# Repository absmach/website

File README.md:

# Abstract Machines Website

Astro + Tailwind source for the [Abstract Machines](https://www.absmach.eu/) website and blog.

## Stack

- Astro (v5)
- Tailwind CSS

## Project Structure

- `src/pages/`: Routes (Astro pages).
- `src/components/`: Shared UI components.
- `src/layouts/`: Page layouts.
- `src/styles/`: Identity stylesheets (`identity-*.css`) shared by the layout and pages.
- `src/content/blogs/`: Blog posts (Markdown).
- `src/content.config.ts`: Blog frontmatter schema.
- `public/`: Static assets (images, favicons, etc).

## Development

```bash
npm install
npm run dev
```

Astro runs on `http://localhost:4321` by default.

During development, images and videos missing from `public/` are fetched from
`https://www.absmach.eu`, so the logo and background animations work without local
R2 credentials. An internet connection is required for these assets.

## Build & Preview

### Public website

The applied AI design is the public website at `http://localhost:4321/`.
It uses AM blue, self-hosted typography, a full-screen Paris architecture film,
and editorial photography.

- `/`: homepage, selected work, and product catalogue.
- `/products/`: searchable AI, Infrastructure, and Hardware categories.
- `/products/{slug}/`: eleven product pages, including Propeller.
- `/research/` and `/research/{elastic,confidential6g}/`: research programmes.
- `/company/`: company background and engineering approach.
- `/stories/{nokia,intel,ericsson,target}/`: sourced engineering stories.
- `/contact/`: enquiry form with product and topic preselection.

The contact form submits to the existing `/api/contact` endpoint. SMTP settings
and delivery requirements are described below. Local browser checks should
intercept submissions rather than sending real mail.

The former `/preview/ai/` page routes redirect permanently to the public pages.
Existing product URLs continue to resolve; `/synth`, `/projects`, and the two
project detail URLs redirect to their new counterparts. Redirects cover both trailing-slash forms and are excluded
from the sitemap. Public pages have canonical URLs, social metadata, and no
preview-only indexing restriction. Blog posts, guides, solutions, pricing,
legal pages, RSS, and documentation remain available at their existing URLs.

`IdentityLayout.astro` owns the main navigation, footer, and public metadata.
The product catalogue lives in `src/data/identity-products.ts`; product pages
and portfolio cards share `ProductVisual.astro`. The homepage and portfolio
show four AI products, four Infrastructure products, and three Hardware products.

Product tabs, category search, mobile navigation, video controls, and media
credits work across the public pages. The silent video pauses offscreen and
when the tab is hidden. Reduced-motion and Save-Data preferences keep the still
poster until the visitor chooses to play.

Existing media URLs remain at `public/preview/ai/media/` to preserve asset
caching. The optimized Paris film is approximately 2.9 MB; editorial photos are
WebP. `src/data/identity-photos.ts` supplies image attributes from the manifest
used by the footer credits. Attribution and source/license records are in
`video-source.json` and `photos-sources.json`. Product imagery and artwork are
recorded in `media/products/sources.json`; project, story, and membership
provenance is stored in their respective media folders. Font licenses and
source records remain in `public/preview/ai/fonts/`.

### Production build

```bash
npm run build
npm run check:site
npm run preview
```

## Cloudflare Scripts

Use the package scripts for Pages Functions workflows:

```bash
npm run cf:dev
npm run cf:deploy
```

- `cf:dev`: Builds the site and starts local Pages dev server from `dist/` using `wrangler.jsonc`.
- `cf:deploy`: Builds and deploys `dist/` to the `absmach` Cloudflare Pages project using `wrangler.jsonc`.

Note: `wrangler pages deploy` does not accept compatibility flags as CLI arguments. Keep them in `wrangler.jsonc` and in Cloudflare Pages project settings.

`wrangler.jsonc` (project config):

- `name`: Cloudflare Pages project name (the `*.pages.dev` subdomain).
- `pages_build_output_dir`: deploy output directory (`./dist`).
- `compatibility_date` and `compatibility_flags` (for example `nodejs_compat`) for Functions runtime.
- `vars`: non-secret defaults for Functions (for contact form, use `TEAM_CONTACT_EMAIL` and `MAIL_FROM_EMAIL`).

Wrangler automatically reads `wrangler.jsonc` when commands are run from the project root.

## Contact Form API (Cloudflare Pages Function)

The contact page submits to `POST /api/contact` via `src/pages/api/contact.js`.
The endpoint uses `nodemailer` over SMTP (Google SMTP supported).
Each successful submission sends:

- one email to your team inbox (`TEAM_CONTACT_EMAIL`)
- one confirmation copy to the user who submitted the form email

Request payload fields:

- `name`
- `email`
- `message`

Required environment variables:

- `SMTP_HOST`: SMTP server host (for Google: `smtp.gmail.com`).
- `SMTP_PORT`: SMTP server port (`465` for SSL, `587` for STARTTLS).
- `SMTP_SECURE`: `true` when using SSL port (usually `465`), otherwise `false`.
- `SMTP_USER`: SMTP username (for Google: full Gmail/Workspace email).
- `SMTP_PASS`: SMTP password (for Google: app password).
- `MAIL_FROM_EMAIL`: From address used when sending both emails.
- `TEAM_CONTACT_EMAIL`: Team inbox that receives contact requests.

For local `smtp4dev` testing (Docker `-p 2525:25`), use:

```bash
SMTP_HOST=127.0.0.1
SMTP_PORT=2525
SMTP_SECURE=false
SMTP_USER=
SMTP_PASS=
MAIL_FROM_EMAIL=info@absmach.eu
TEAM_CONTACT_EMAIL=info@absmach.eu
```

`SMTP_USER` and `SMTP_PASS` are optional for local test servers.

For Cloudflare Pages production:

- Non-secret values are already in `wrangler.jsonc` under `vars`:
  `SMTP_HOST`, `SMTP_PORT`, `SMTP_SECURE`, `MAIL_FROM_EMAIL`, `TEAM_CONTACT_EMAIL`.
- Set only SMTP credentials as secrets on the project:

```bash
wrangler pages secret put SMTP_USER
wrangler pages secret put SMTP_PASS
```

Backward compatibility: `NO_REPLY_EMAIL`, `CONTACT_FROM_EMAIL`, and `CONTACT_TO_EMAIL` are still accepted, but new projects should use `MAIL_FROM_EMAIL` and `TEAM_CONTACT_EMAIL`.

Production does not use `.dev.vars`.

- `.dev.vars` is local-only for `wrangler pages dev`.
- For production, configure values in Cloudflare Pages:
  Dashboard -> Pages -> your project -> Settings -> Variables and Secrets -> Production.
- No separate production env file is required in the repo.

For local Cloudflare Pages function testing, copy `.dev.vars.example` to `.dev.vars` and fill the values.

`nodemailer` requires Node compatibility in Cloudflare Workers. Enable `nodejs_compat`:

- In Cloudflare Pages project settings: Workers runtime compatibility flags.
- Or in local dev: `wrangler pages dev dist --compatibility-flag=nodejs_compat`.

## Images

Images are served from Cloudflare R2 (not committed to this repo) via
`src/pages/img/[...path].ts`, which keeps existing `/img/...` URLs working unchanged.
Maintainers publishing new/updated images: see [scripts/README.md](scripts/README.md).

## Blog

See [WRITING.md](WRITING.md) for frontmatter and writing guidelines.

## Sitemap / robots.txt

- `@astrojs/sitemap` generates `dist/sitemap-index.xml` (and chunk files like `dist/sitemap-0.xml`) during `npm run build`.
- `src/pages/robots.txt.ts` is prerendered as `/robots.txt` and points to `/sitemap-index.xml`.

## RSS

- `src/pages/rss.xml.ts` is prerendered as `/rss.xml` (blog feed).

## Documentation

- [How to Write a Blog Post](WRITING.md)
- [Publishing Images (maintainers)](scripts/README.md)

## Legal document scope

The company website’s `/terms/` covers website use, not all product contracts.
Atomic terms and privacy information remain on `atomicapp.dev/legal/`.
`/privacy/` describes company-site visits and enquiries. `/imprint/` identifies
the publisher and host. General and legal enquiries use `info@absmach.eu`; privacy
requests use `privacy@absmach.eu`. No voluntary uptime, support, return or warranty
period is offered by these website documents. Existing accepted customer agreements
are not amended by these edits.

Supplier transfer arrangements, actual mailbox/log retention and edge-injected
tracking must be checked against production configuration. A public company business
telephone remains to be supplied; the publisher’s private number is not published.
These content corrections do not certify operational compliance.

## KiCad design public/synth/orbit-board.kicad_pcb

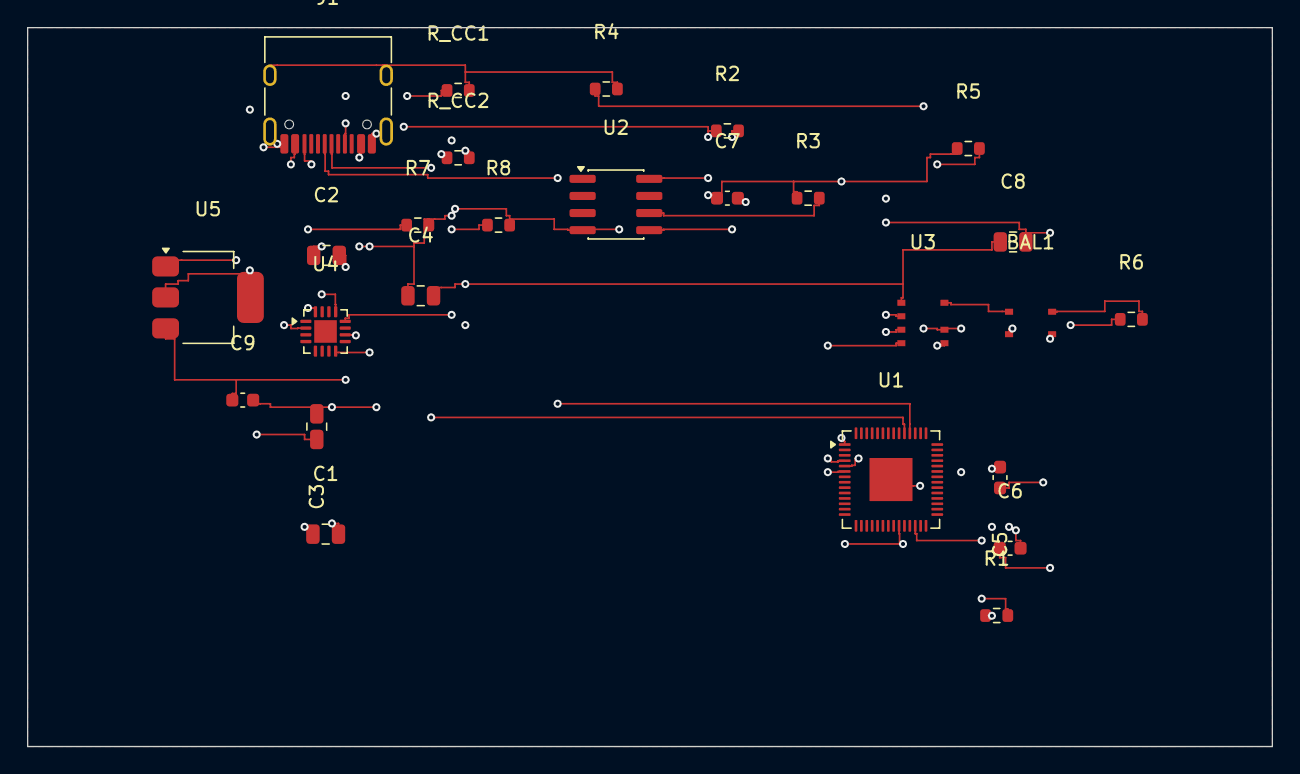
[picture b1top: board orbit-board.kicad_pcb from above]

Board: 4 copper layers, 92.5 x 53.4 mm, 26 parts (0 on the bottom side), 21 nets.

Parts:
BAL1: balun_2g4; Johanson_0805
C1, C2, C3, C4, C8: c_generic_0805; C_0805_2012Metric
C5, C6, C7, C9: c_generic_0603; C_0603_1608Metric
J1: usb_c_receptacle; USB_C_Receptacle_HRO_TYPE-C-31-M-12
R1, R2, R3, R4, R5, R6, R7, R8: r_generic_0603; R_0603_1608Metric
R_CC1, R_CC2: r_generic_0603; R_0603_1608Metric
U1: rp2350; QFN-56-1EP_7x7mm_P0.4mm_EP3.2x3.2mm
U2: atecc608; SOIC-8_3.9x4.9mm_P1.27mm
U3: bg95; Quectel_BG95-M3
U4: bq24074; VQFN-16-1EP_3x3mm_P0.5mm_EP1.68x1.68mm
U5: ams1117_3v3; SOT-223-3_TabPin2

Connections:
net_0: C1.1, J1.A4, J1.A9, J1.B4, J1.B9, U4.13
net_1: BAL1.4, C1.2, C2.2, C3.2, C4.2, C5.2, C6.2, C7.2, C8.2, C9.2, J1.A1, J1.A12, J1.B1, J1.B12, J1.SH, R4.2, R7.2, R8.2, R_CC1.2, R_CC2.2, U1.57, U2.4, U3.3, U4.8, U4.17, U5.1
net_2: J1.A5, R_CC1.1
net_3: J1.B5, R_CC2.1
net_4: C2.1, C9.1, U4.10, U5.3
net_5: C3.1, C5.1, C6.1, C7.1, R1.1, R2.1, R3.1, R5.1, U1.1, U1.23, U1.43, U1.44, U1.48, U2.8, U5.2
net_6: C4.1, C8.1, U3.32, U4.2
net_7: R7.1, U4.16
net_8: R8.1, U4.12
net_9: R1.2, U1.26
net_10: R2.2, U1.2, U2.5
net_11: R3.2, U1.3, U2.6
net_12: R4.1, U1.6, U3.15
net_13: U1.4, U3.34
net_14: U1.5, U3.35
net_15: BAL1.1, U3.60
net_16: BAL1.2, R6.1
net_17: BAL1.3, R6.2
net_18: R5.2, U3.17
net_19: J1.A6, U1.47
net_20: J1.A7, U1.46

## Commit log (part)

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2026-03-11 docs(blog): rename Proplet to Propeller in TEE article
2026-03-11 docs(blog): update title, description, and Propeller details
2026-03-11 Rename images and update references
2026-03-11 docs(blog): fix architecture image to move KSB out of tee
2026-03-12 add a changelog blog
2026-03-12 update date
2026-03-12 add requested changes
2026-03-16 initial implementation
2026-03-18 first blog draft
2026-03-18 update package json package manager
2026-03-19 add blog images
2026-03-19 fix date
2026-03-19 remove empty space
2026-03-23 add access control blog
2026-03-24 Add SuperMQ and Magistrala merge announcement blog post
2026-03-24 Add SuperMQ and Magistrala unified platform detailed blog post
2026-03-24 remove section
2026-03-24 Add cover image and fix image path for merge announcement blog
2026-03-25 Add cover image and fix image path for unified blog post
2026-03-27 Remove featured flag and add Abstract Machines stack description
2026-03-30 Remove SuperMQ references and update to Magistrala only
    - Replace all SuperMQ mentions with Magistrala throughout the blog
    - Update excerpt and descriptions to reflect unified platform
    - Remove 'built on SuperMQ' phrasing since platforms are now merged
    - Fix duplicate text and formatting issues in Domains section
2026-03-30 Update architecture diagram for access control blog
2026-04-01 address comments
2026-04-02 update date to 2nd April
2026-04-02 add agent blog
2026-04-02 remove docs links
2026-04-06 Add SuperMQ and Magistrala merge announcement blog post (#112)
    * Add SuperMQ and Magistrala merge announcement blog post
    * Add cover image and fix image path for merge announcement blog
    * Remove featured flag and add Abstract Machines stack description
    * address comments
    ---------
2026-04-07 SEO improvements: add llms.txt, meta descriptions, and schema updates for absmach.eu
2026-04-07 Fix SEO issues: canonical URLs, OG images, JSON-LD schemas, and title tags
2026-04-07 SEO report fixes
2026-04-07 Update merge blog
2026-04-07 NOISSUE - Update merger blog
2026-04-07 update cover page
2026-04-07 add new image
2026-04-09 add smart water metering blog
2026-04-09 make blog more professional
2026-04-10 add magistrala as a framework blog
2026-04-10 vault migration
2026-04-10 update wording
2026-04-13 update the date to 13th
2026-04-14 remove package lock and stick to pnpm as package manager
2026-04-20 add announcement blog
2026-04-21 empty commit to triggering CF build
2026-04-21 update number of deployments
2026-04-21 add solution packs blog
2026-04-22 fix: update intro line
2026-04-27 fix wording
2026-04-27 add best iot platforms in 2026 blog
2026-04-27 NOISSUE - Update fml blog to reflect implementation
2026-04-27 NOISSUE - Replace cover image and clean up asset names
    - Replace Federated__Machine_Learning.jpg cover with propeller-fml-mental-model.svg
    - Strip federated-ml prefix from all blog image filenames
    - Update fml.md image references to match renamed files
    - Add centralized-training-data.xml draw.io source diagram
2026-04-27 Add fml blog
    Update blog post
    Add images
    Add images
    Address comments
    Address comments
    Address comments
2026-04-27 NOISSUE - Clean up blog image names
    Remove fml/federated prefixes from remaining image filenames,
    delete unused jpg cover, and update references in fml.md.
2026-04-27 fix: update content accuracy and add external links
2026-04-27 fix: update date
2026-04-27 NOISSUE - Remove centralized-training-data.xml
2026-04-28 NOISSUE - Add fML blog (#81)
    * Add fml blog
    Update blog post
    Add images
    Add images
    Address comments
    Address comments
2026-04-28 supermq to magistrala naming changeover
2026-04-30 updated blog with migrations
2026-04-30 add migration blog
2026-04-30 update the image
2026-04-30 NOISSUE - Add migration blog for v0.20.0 (#139)
2026-04-30 change the link to blog
2026-04-30 Add v0.20.0 release blog (#134)
    * add announcement blog
    * update wording
    * address comments
    * updated blog with migrations
    * fix wording
    * update the image
2026-04-30 remove featured option
2026-04-30 add matrix link
2026-04-30 NOISSUE - Update blog (#140)
    * remove featured option
    * add matrix link
    ---------
2026-05-05 update rules engine description
2026-05-05 update when not to section for magistrala
2026-05-05 MG-137 - Add best IoT platforms in 2026 blog (#138)
    * add best iot platforms in 2026 blog
    * fix: update content accuracy and add external links
    * fix: update date
    * update rules engine description
    * update when not to section for magistrala
    ---------
2026-05-05 update blog for best iot platform in 2026
2026-05-06 MG-137 - Add best IoT platforms in 2026 blog (#138)
2026-05-06 update screenshots
2026-05-06 add tags
2026-05-06 update alts for the image
2026-05-06 add links
2026-05-07 Add FluxMQ dashboard blog (#114)
    * add flux dashbord blog
    * update screenshots
    * add tags
    * update alts for the image
    * add links
    * update date
2026-05-07 update solutions, services, projects,company and contact pages
2026-05-07 fix SEO and add docs to navbar
2026-05-07 update navbar dropdowns
2026-05-07 remove extra services from navbar
2026-05-07 update fluxmq logo and colors
2026-05-07 fix hero sections for product pages
2026-05-07 remove blue accent
2026-05-07 add global deployments
2026-05-07 utilize magistrala blue theme
2026-05-07 update the blue theme to be more distinct
2026-05-10 fix mobile responsiveness
2026-05-11 update SEO and performance
2026-05-11 fix icon visibility
2026-05-12 migration from s0 to a0
2026-05-19 add atom and quarc
2026-05-19 update deployments cards
2026-05-19 update product cards
2026-05-19 update hero image
2026-05-19 add lucide icons
2026-05-20 fix icons
2026-05-20 allow for quick theme switching
2026-05-20 Unification deployment (#144)
    * update homepage, products, blog pages
    * update solutions, services, projects,company and contact pages
    * remove extra services from navbar
    * update navbar dropdowns
    * fix SEO and add docs to navbar
    * fix hero sections for product pages
2026-05-22 add hardware page
2026-05-22 NOISSUE - Add hardware page (#146)
2026-05-22 fix quarc header description
2026-05-22 fix quarc header description (#147)
2026-05-22 fix website open-graph image
2026-05-22 fix website open-graph image (#148)
2026-05-25 fix urls
2026-05-25 fix urls (#149)
2026-05-25 fix links in blogs
2026-05-25 fix links in blogs (#150)
2026-05-25 fix abstract machines links
2026-05-25 fix abstract machines links (#151)
2026-05-26 fix mobile responsiveness for product pages
2026-05-26 fix mobile hero logo/name sizing across product pages
2026-05-26 update propeller hero section image from being clipped
2026-05-26 still show hero image in mobile mode
2026-05-26 fix organization level SEO
2026-05-26 fix product pages SEO
2026-05-26 fix heading hierarchy, keyword H2s, and internal linking
2026-05-26 fix finalcta enterprise card
2026-05-26 fix image and video CLS — add width/height attributes across all hero videos and Magistrala feature images
2026-05-26 fix mobile touch targets for blog pillar chips
2026-05-29 fix Magistrala product page SEO
2026-05-29 fix FluxMQ product page SEO
2026-05-29 fix atom product page SEO
2026-05-29 update A0 product SEO
2026-05-29 update propeller image
2026-05-29 separate propeller hero section image
2026-05-29 update propeller product page SEO
2026-05-29 remove unused architecture image
2026-05-29 add internal cross-links across product pages for pillar-cluster SEO
2026-06-02 make documentation pri cta for fluxmq
2026-06-02 add github links and make docs cta for flux
2026-06-02 update atom and propeller ctas
2026-06-04 fix solutions link to cloud
2026-06-05 NOISSUE - Update SEO (#152)
    * fix organization level SEO
    * fix product pages SEO
    * fix heading hierarchy, keyword H2s, and internal linking
    * fix finalcta enterprise card
    * fix image and video CLS — add width/height attributes across all hero videos and Magistrala feature images
    * fix mobile touch targets for blog pillar chips
2026-06-08 update sitemap file
2026-06-08 update sitemap file (#155)
2026-06-08 fix lint and formating issues
2026-06-08 update package manager version
2026-06-08 add workspace manager
2026-06-08 add node to allowed builds
2026-06-08 fix format errors
2026-06-08 fix format check
2026-06-09 NOISSUE - Remove CD, add CI, fix lint and format issues (#156)
    * fix lint and formating issues
    * update package manager version
    * add workspace manager
    * add node to allowed builds
    * fix format errors
    * fix format check
2026-06-10 add pillar pages
2026-06-12 add atom announcement blog
2026-06-12 add atom category
2026-06-12 fix formatting
2026-06-12 add ui screenshots
2026-06-12 Improve text
2026-06-12 remove scrollbar in playground image
2026-06-12 fix consecutive images to a grid format
2026-06-12 replace playground image with create role image
2026-06-12 NOISSUE - Add Atom announcement blog (#158)
    * add atom announcement blog
    * add atom category
    * fix formatting
    * add ui screenshots
    * Improve text
    * remove scrollbar in playground image
2026-06-15 add getting started with atom blog
2026-06-15 fix curl commands
2026-06-15 add mermaid functionality
2026-06-15 add atom docs to header link
2026-06-15 add getting started link in atom announcement
2026-06-15 add atom docs to header link (#160)
2026-06-15 add blog on why split identity and auth breaks at scale
2026-06-15 add mermaid rendering option
2026-06-15 move architecture diagram to beginning of tutorial
2026-06-15 NOISSUE - SEO: add comparison pages, IIoT pillar page, and on-page optimisations (#157)
    * add pillar pages
    * fix format check
    ---------
2026-06-17 update atom tutorial screenshots and prose
    Replace all dark-theme screenshots with light-theme versions and
    rename them by dropping the -light suffix. Remove old screenshots
    from the previous tutorial iteration. Replace em dashes throughout
    the prose with colons, semicolons, parentheses, or sentence breaks.
2026-06-17 remove the resource type diagram
2026-06-17 update content
2026-06-17 update image zoom
2026-06-17 remove dark theme
2026-06-20 improve cover image to check for format
2026-06-20 add product og images
2026-06-20 fix mg page to use atom as the access control
2026-06-20 Fix Magistrala page to use Atom as the access control (#163)
2026-06-22 MG-127- Add solution packs blog (#130)
    * add solution packs blog
    * update date
    * fix: update intro line
    ---------
2026-06-22 Update getting-started-with-atom tutorial and add copy buttons to blog code blocks
2026-06-22 NOISSUE - Add getting started with Atom blog (#159)
    * add getting started with atom blog
    * add mermaid functionality
    * fix curl commands
    * add getting started link in atom announcement
    * move architecture diagram to beginning of tutorial
    * update atom tutorial screenshots and prose
2026-06-22 Add blog post: introducing-propeller
2026-06-22 Fix blog frontmatter: add required author field
2026-06-22 Fix Prettier formatting
2026-06-22 BeagleV Fire wlan setup blog
2026-06-22 Add blog post: mqtt-vs-amqp-iot-protocol-comparison-2026
2026-06-22 Add cover image for mqtt-vs-amqp-iot-protocol-comparison-2026
2026-06-22 Update coverImage and ogImage to website paths
2026-06-22 Address PR review comments
2026-06-22 Fix corrupted content: remove preamble and HTML comment
2026-06-23 NOISSUE - Add Connecting BeagleV Fire to Magistrala blog (#82)
    * Add blog: Connecting BeagleV Fire to SuperMQ
    * Review changes
    * Add blog post: Building the S0 (#76)
    * Post rebase: Building the S0
    * Update avatar
    * Post rebase changes
2026-06-26 Add blog post: what-s-new
2026-06-26 add cover image
2026-06-29 fix mermaid diagram
2026-06-30 Add blog post: zephyr-rtos-vs-linux-iot-gateway-a0
2026-06-30 add hero page
2026-06-30 conflict resolve
